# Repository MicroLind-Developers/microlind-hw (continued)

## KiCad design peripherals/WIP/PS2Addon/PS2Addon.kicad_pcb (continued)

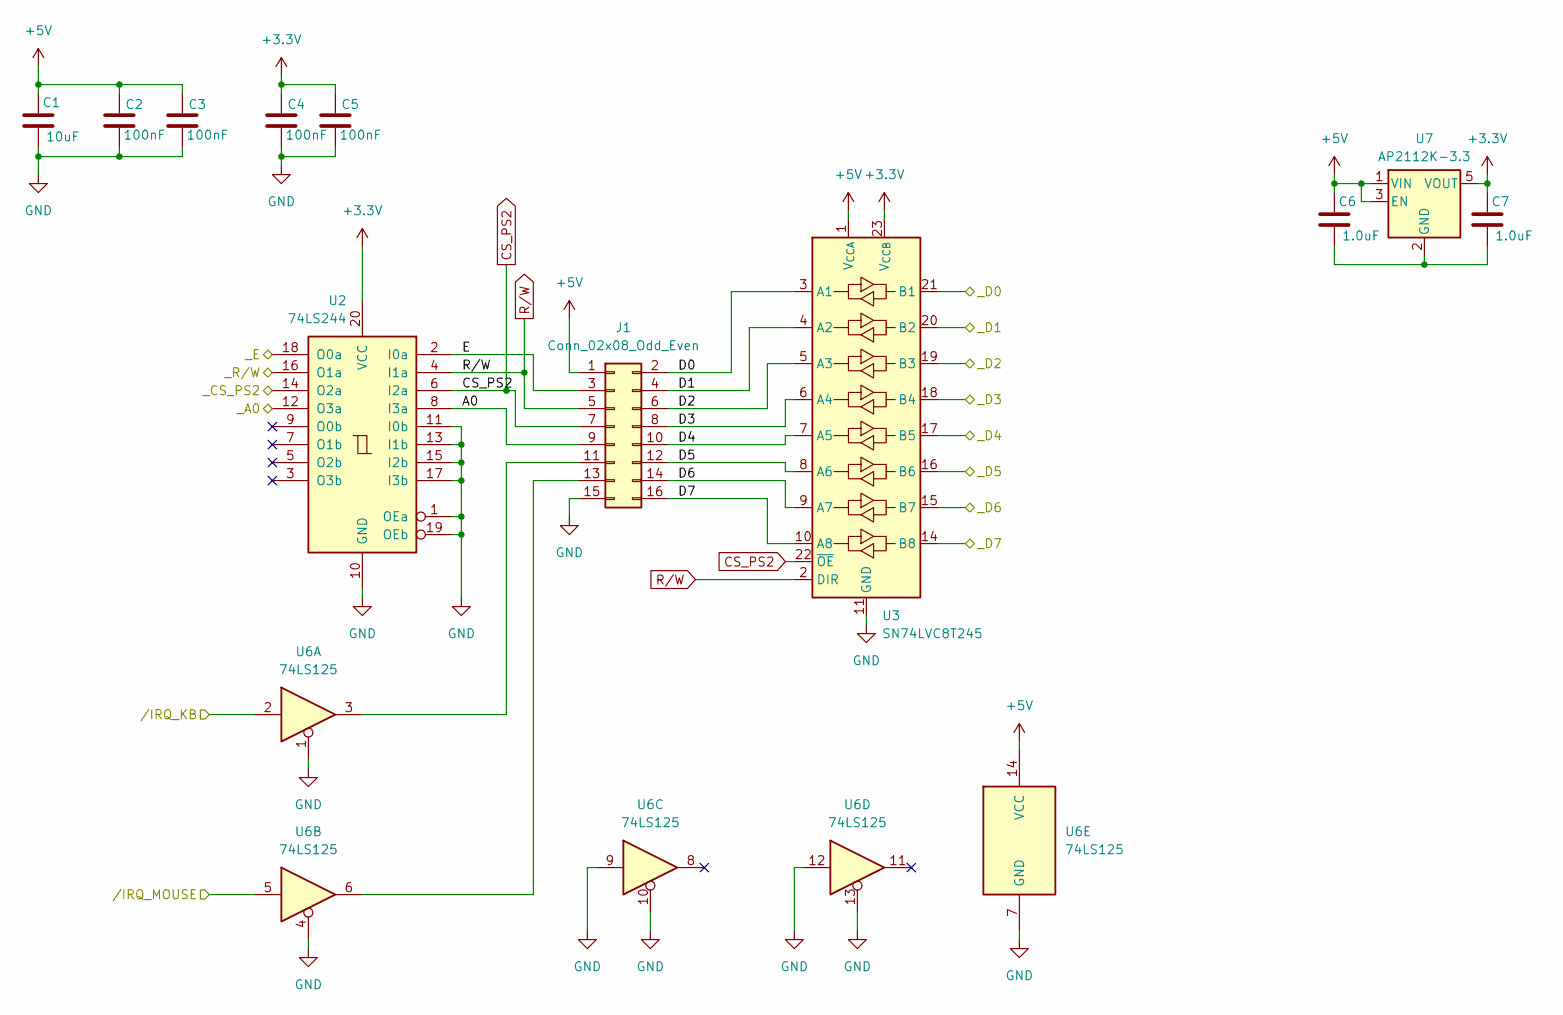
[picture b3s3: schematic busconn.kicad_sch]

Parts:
C1: 10uF; C_0402_1005Metric
C2, C3, C4, C5: 100nF; C_0402_1005Metric
C6, C7: 1.0uF; C_0402_1005Metric
J1: Conn_02x08_Odd_Even; PinHeader_2x08_P2.54mm_Vertical
U2: 74LS244; TSSOP-20_4.4x6.5mm_P0.65mm
U3: SN74LVC8T245; TSSOP-24_6.1x7.8mm_P0.65mm
U6: 74LS125; TSSOP-14_4.4x5mm_P0.65mm
U7: AP2112K-3.3; SOT-23-5

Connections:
+3.3V: C4.1, C5.1, C7.1, U2.20 (VCC), U3.23 (V_{CCB}), U3.24 (V_{CCB}), U7.5 (VOUT); also elsewhere on the board
+5V: C1.1, C2.1, C3.1, C6.1, J1.1, U3.1 (V_{CCA}), U6.14 (VCC), U7.1 (VIN), U7.3 (EN); also elsewhere on the board
/BusConnection/A0: J1.9, U2.8 (I3a)
/BusConnection/D0: J1.2, U3.3 (A1)
/BusConnection/D1: J1.4, U3.4 (A2)
/BusConnection/D2: J1.6, U3.5 (A3)
/BusConnection/D3: J1.8, U3.6 (A4)
/BusConnection/D4: J1.10, U3.7 (A5)
/BusConnection/D5: J1.12, U3.8 (A6)
/BusConnection/D6: J1.14, U3.9 (A7)
/BusConnection/D7: J1.16, U3.10 (A8)
/BusConnection/E: J1.3, U2.2 (I0a)
/BusConnection/_A0: U2.12 (O3a); also elsewhere on the board
/BusConnection/_CS_PS2: U2.14 (O2a); also elsewhere on the board
/BusConnection/_D0: U3.21 (B1); also elsewhere on the board
/BusConnection/_D1: U3.20 (B2); also elsewhere on the board
/BusConnection/_D2: U3.19 (B3); also elsewhere on the board
/BusConnection/_D3: U3.18 (B4); also elsewhere on the board
/BusConnection/_D4: U3.17 (B5); also elsewhere on the board
/BusConnection/_D5: U3.16 (B6); also elsewhere on the board
/BusConnection/_D6: U3.15 (B7); also elsewhere on the board
/BusConnection/_D7: U3.14 (B8); also elsewhere on the board
/BusConnection/_E: U2.18 (O0a); also elsewhere on the board
/BusConnection/_R/W: U2.16 (O1a); also elsewhere on the board
/BusConnection//IRQ_KB: U6.2; also elsewhere on the board
/BusConnection//IRQ_MOUSE: U6.5; also elsewhere on the board
CS_PS2: J1.7, U2.6 (I2a), U3.22 (~OE)
GND: C1.2, C2.2, C3.2, C4.2, C5.2, J1.15, U2.1 (OEa), U2.10 (GND), U2.11 (I0b), U2.13 (I1b), U2.15 (I2b), U2.17 (I3b), U2.19 (OEb), U3.11 (GND), U3.12 (GND), U3.13 (GND), U6.1, U6.4, U6.7 (GND), U6.9, U6.10, U6.12, U6.13; also elsewhere on the board
unnamed: J1.11, U6.3
unnamed: J1.13, U6.6
unnamed: C6.2, C7.2, U7.2 (GND)
R/W: J1.5, U2.4 (I1a), U3.2 (DIR)

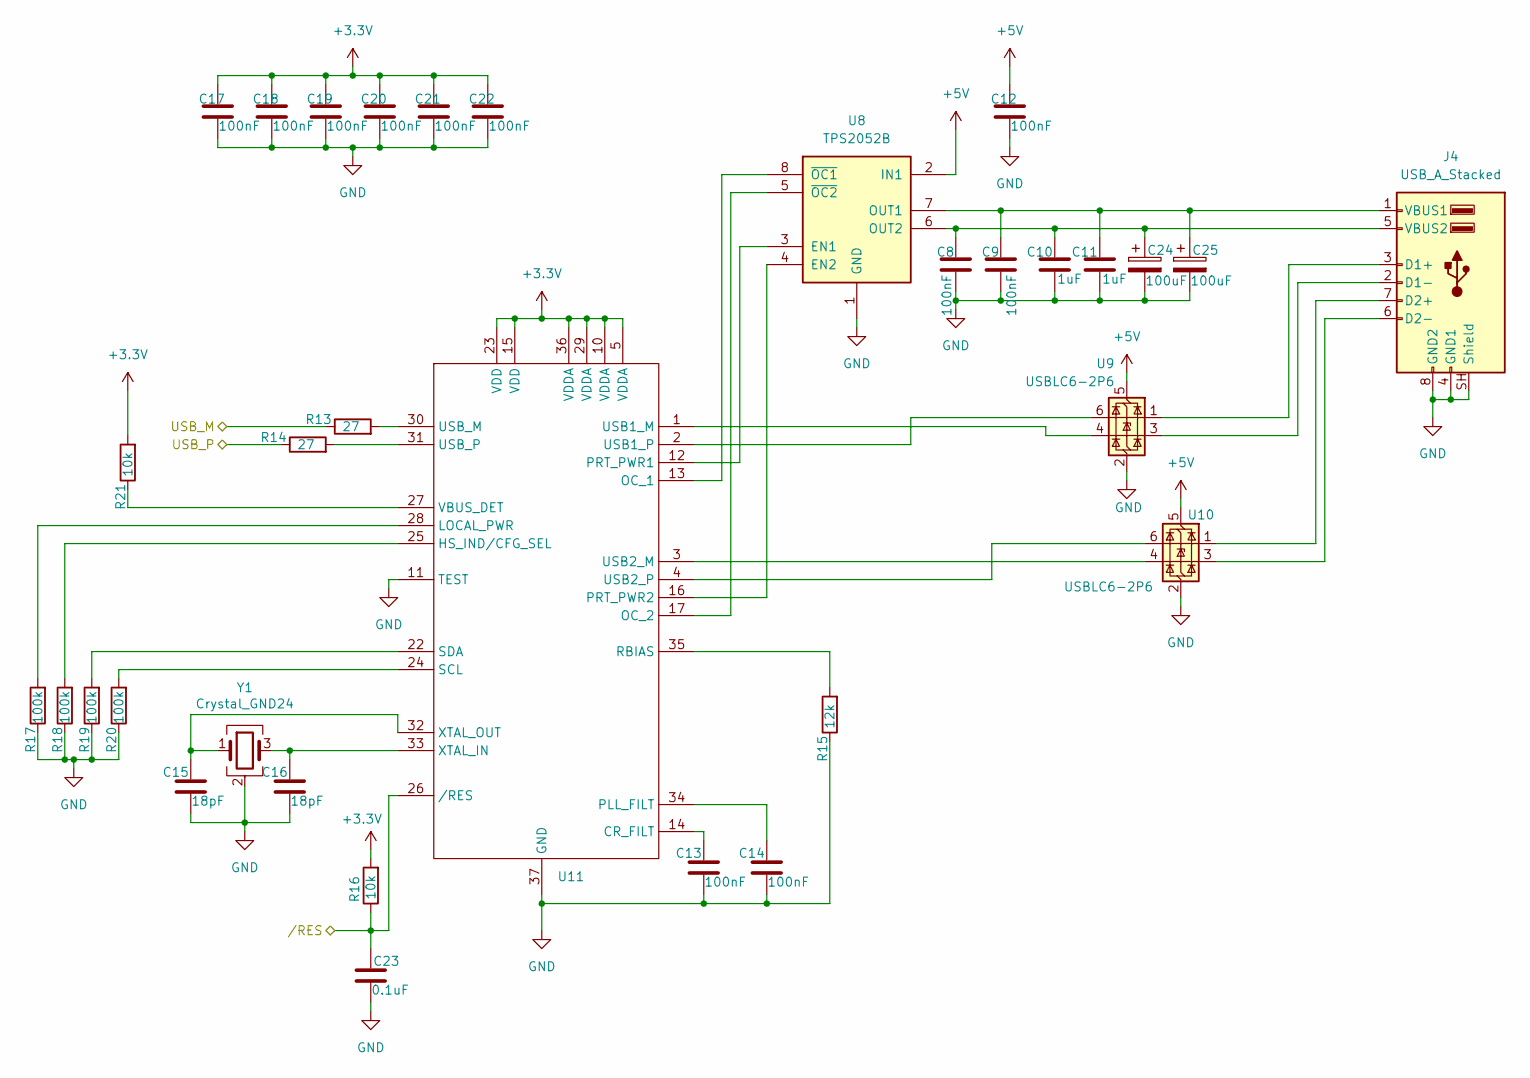
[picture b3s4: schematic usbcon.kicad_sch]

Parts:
C8, C9, C12, C13, C14, C17, C18, C19, C20, C21, C22: 100nF; C_0402_1005Metric
C10, C11: 1uF; C_0402_1005Metric
C15, C16: 18pF; C_0402_1005Metric
C23: 0.1uF; C_0402_1005Metric
C24, C25: 100uF; CP_EIA-1608-08_AVX-J
J4: USB_A_Stacked; USB_A_CUI_UJ2-ADH-TH_Horizontal_Stacked
R13, R14: 27; R_0402_1005Metric
R15: 12k; R_0402_1005Metric
R16, R21: 10k; R_0402_1005Metric
R17, R18, R19, R20: 100k; R_0402_1005Metric
U8: TPS2052B; SOIC-8_3.9x4.9mm_P1.27mm
U9, U10: USBLC6-2P6; SOT-666
U11: QFN-36-1EP_6x6mm_P0.5mm_EP4.1x4.1mm_ThermalVias
Y1: Crystal_GND24; Crystal_SMD_2520-4Pin_2.5x2.0mm

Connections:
+3.3V: C17.1, C18.1, C19.1, C20.1, C21.1, C22.1, R16.2, R21.2, U11.5 (VDDA), U11.10 (VDDA), U11.15 (VDD), U11.23 (VDD), U11.29 (VDDA), U11.36 (VDDA); also elsewhere on the board
+5V: C12.1, U8.2 (IN1), U9.5 (VBUS), U10.5 (VBUS); also elsewhere on the board
/USBConnector/USB_M: R13.1; also elsewhere on the board
/USBConnector/USB_P: R14.1; also elsewhere on the board
GND: C8.2, C9.2, C10.2, C11.2, C12.2, C13.2, C14.2, C15.2, C16.2, C17.2, C18.2, C19.2, C20.2, C21.2, C22.2, C23.2, C24.2, C25.2, J4.4 (GND1), J4.8 (GND2), J4.SH (Shield), R15.1, R17.1, R18.1, R19.1, R20.1, U8.1 (GND), U9.2 (GND), U10.2 (GND), U11.11 (TEST), U11.37 (GND), Y1.2 (G), Y1.4 (G); also elsewhere on the board
unnamed: J4.3 (D1+), U9.1 (I/O1)
unnamed: J4.2 (D1-), U9.3 (I/O2)
unnamed: J4.7 (D2+), U10.1 (I/O1)
unnamed: J4.6 (D2-), U10.3 (I/O2)
unnamed: C9.1, C11.1, C25.1, J4.1 (VBUS1), U8.7 (OUT1)
unnamed: C8.1, C10.1, C24.1, J4.5 (VBUS2), U8.6 (OUT2)
unnamed: C13.1, U11.14 (CR_FILT)
unnamed: R18.2, U11.25 (HS_IND/CFG_SEL)
unnamed: R17.2, U11.28 (LOCAL_PWR)
unnamed: U8.8 (~OC1), U11.13 (OC_1)
unnamed: U8.5 (~OC2), U11.17 (OC_2)
unnamed: C14.1, U11.34 (PLL_FILT)
unnamed: U8.3 (EN1), U11.12 (PRT_PWR1)
unnamed: U8.4 (EN2), U11.16 (PRT_PWR2)
unnamed: R15.2, U11.35 (RBIAS)
unnamed: R20.2, U11.24 (SCL)
unnamed: R19.2, U11.22 (SDA)
unnamed: U9.4 (I/O2), U11.1 (USB1_M)
unnamed: U9.6 (I/O1), U11.2 (USB1_P)
unnamed: U10.4 (I/O2), U11.3 (USB2_M)
unnamed: U10.6 (I/O1), U11.4 (USB2_P)
unnamed: R13.2, U11.30 (USB_M)
unnamed: R14.2, U11.31 (USB_P)
unnamed: R21.1, U11.27 (VBUS_DET)
unnamed: C16.1, U11.33 (XTAL_IN), Y1.3
unnamed: C15.1, U11.32 (XTAL_OUT), Y1.1
/USB_RES: C23.1, R16.1, U11.26 (/RES); also elsewhere on the board

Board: 2 copper layers, 82 parts (0 on the bottom side), 80 nets, no tracks yet.

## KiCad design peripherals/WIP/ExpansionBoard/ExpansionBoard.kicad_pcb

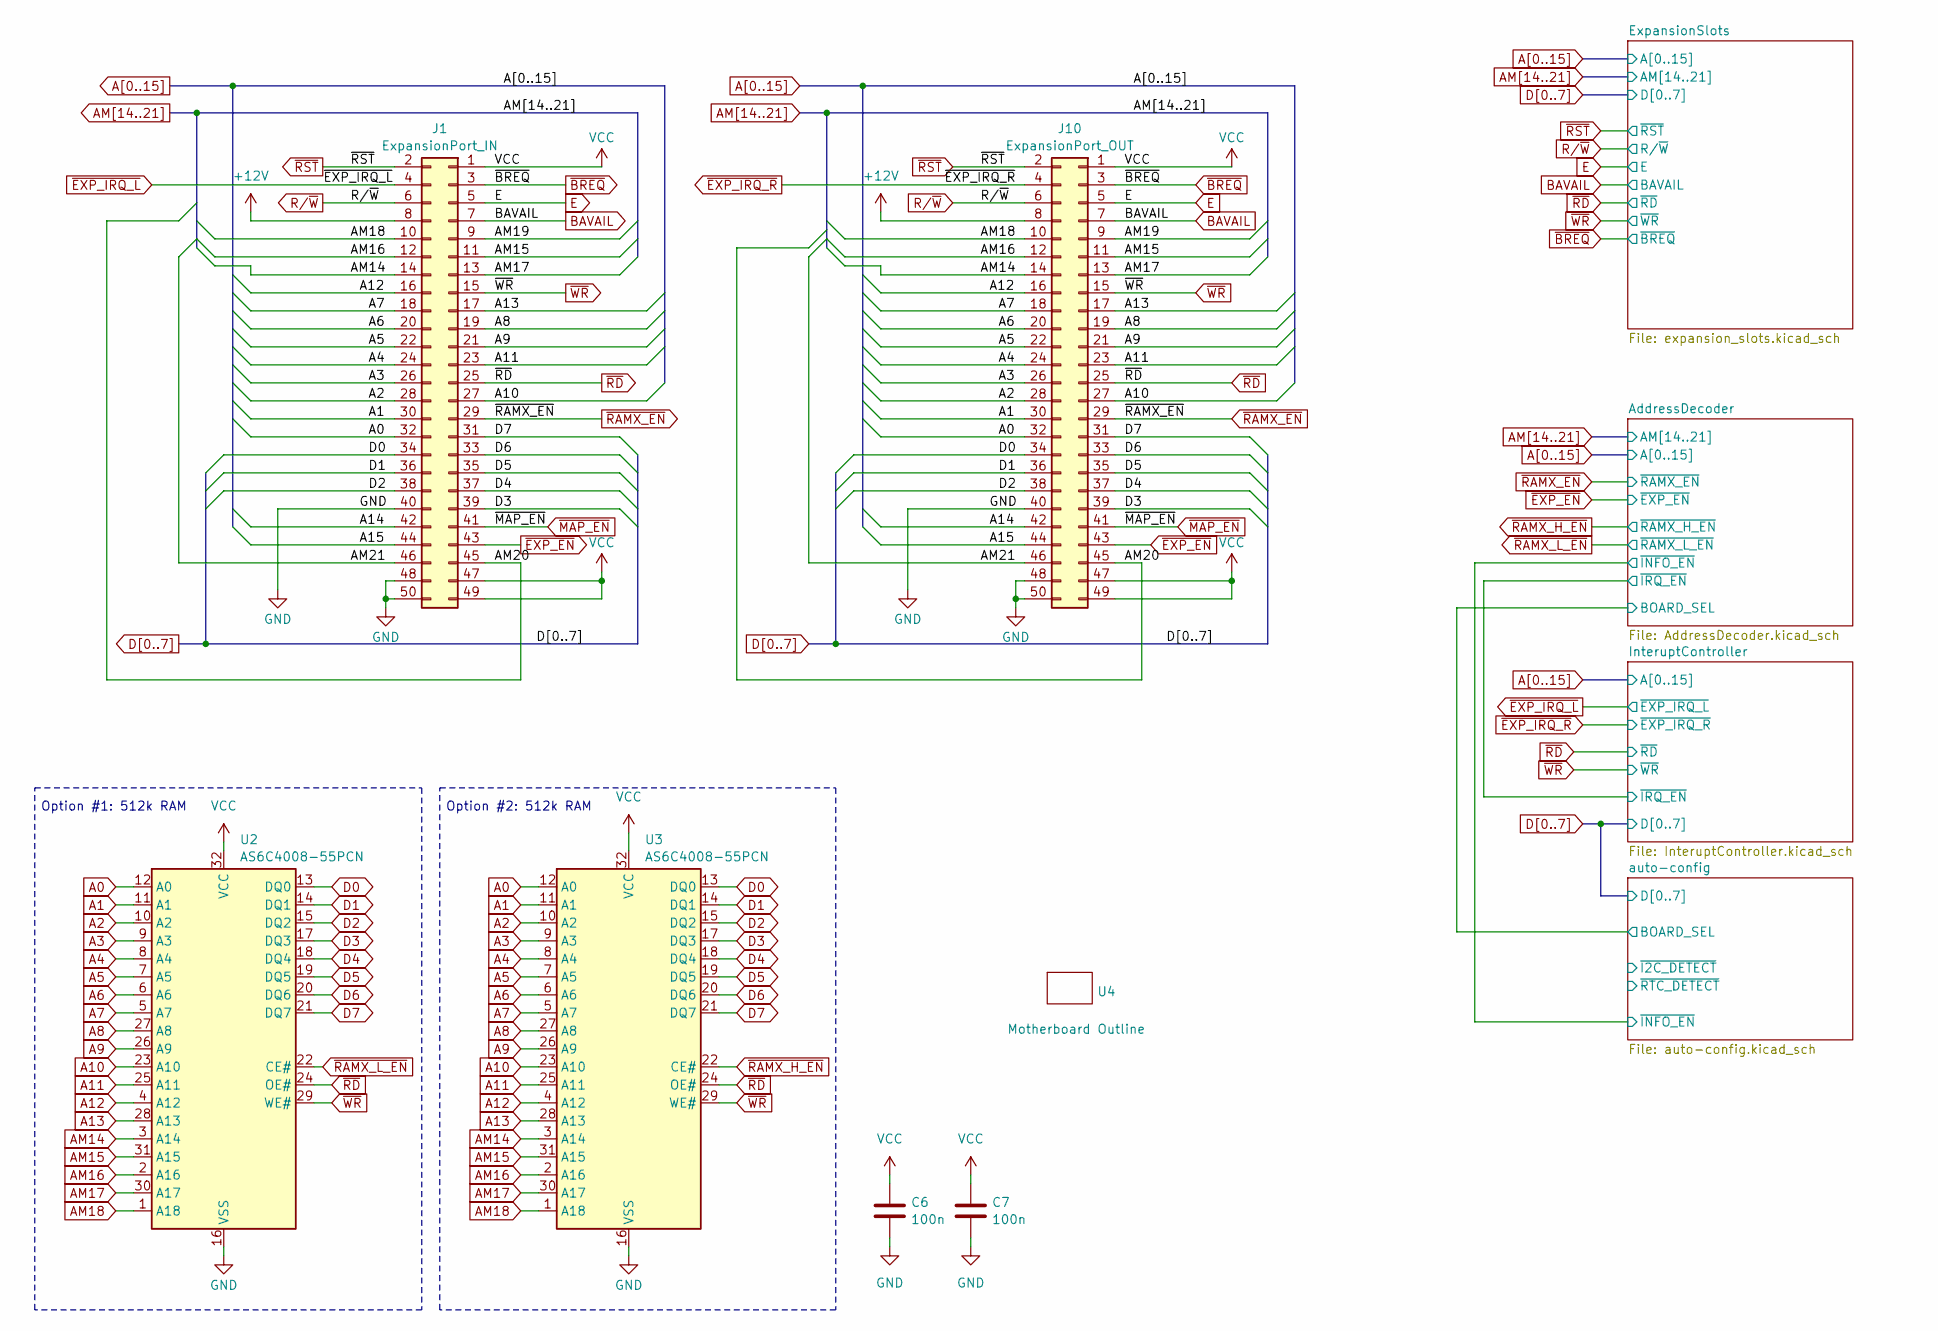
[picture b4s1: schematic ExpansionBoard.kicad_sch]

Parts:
C6, C7: 100n; C_Disc_D3.0mm_W1.6mm_P2.50mm
J1: ExpansionPort_IN; PinSocket_2x25_P2.54mm_Vertical
J10: ExpansionPort_OUT; PinSocket_2x25_P2.54mm_Vertical
U2, U3: AS6C4008-55PCN; DIP-32_W15.24mm_Socket
U4: Motherboard Outline; mITX

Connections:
+12V: J1.8, J10.8; also elsewhere on the board
A0: J1.32, J10.32, U2.12 (A0), U3.12 (A0); also elsewhere on the board
A1: J1.30, J10.30, U2.11 (A1), U3.11 (A1); also elsewhere on the board
A2: J1.28, J10.28, U2.10 (A2), U3.10 (A2); also elsewhere on the board
A3: J1.26, J10.26, U2.9 (A3), U3.9 (A3); also elsewhere on the board
A4: J1.24, J10.24, U2.8 (A4), U3.8 (A4); also elsewhere on the board
A5: J1.22, J10.22, U2.7 (A5), U3.7 (A5); also elsewhere on the board
A6: J1.20, J10.20, U2.6 (A6), U3.6 (A6); also elsewhere on the board
A7: J1.18, J10.18, U2.5 (A7), U3.5 (A7); also elsewhere on the board
A8: J1.19, J10.19, U2.27 (A8), U3.27 (A8); also elsewhere on the board
A9: J1.21, J10.21, U2.26 (A9), U3.26 (A9); also elsewhere on the board
A10: J1.27, J10.27, U2.23 (A10), U3.23 (A10); also elsewhere on the board
A11: J1.23, J10.23, U2.25 (A11), U3.25 (A11); also elsewhere on the board
A12: J1.16, J10.16, U2.4 (A12), U3.4 (A12); also elsewhere on the board
A13: J1.17, J10.17, U2.28 (A13), U3.28 (A13); also elsewhere on the board
A14: J1.42, J10.42; also elsewhere on the board
A15: J1.44, J10.44; also elsewhere on the board
AM14: J1.14, J10.14, U2.3 (A14), U3.3 (A14); also elsewhere on the board
AM15: J1.11, J10.11, U2.31 (A15), U3.31 (A15); also elsewhere on the board
AM16: J1.12, J10.12, U2.2 (A16), U3.2 (A16); also elsewhere on the board
AM17: J1.13, J10.13, U2.30 (A17), U3.30 (A17); also elsewhere on the board
AM18: J1.10, J10.10, U2.1 (A18), U3.1 (A18); also elsewhere on the board
AM19: J1.9, J10.9; also elsewhere on the board
AM20: J1.45, J10.45; also elsewhere on the board
AM21: J1.46, J10.46; also elsewhere on the board
BAVAIL: J1.7, J10.7; also elsewhere on the board
D0: J1.34, J10.34, U2.13 (DQ0), U3.13 (DQ0); also elsewhere on the board
D1: J1.36, J10.36, U2.14 (DQ1), U3.14 (DQ1); also elsewhere on the board
D2: J1.38, J10.38, U2.15 (DQ2), U3.15 (DQ2); also elsewhere on the board
D3: J1.39, J10.39, U2.17 (DQ3), U3.17 (DQ3); also elsewhere on the board
D4: J1.37, J10.37, U2.18 (DQ4), U3.18 (DQ4); also elsewhere on the board
D5: J1.35, J10.35, U2.19 (DQ5), U3.19 (DQ5); also elsewhere on the board
D6: J1.33, J10.33, U2.20 (DQ6), U3.20 (DQ6); also elsewhere on the board
D7: J1.31, J10.31, U2.21 (DQ7), U3.21 (DQ7); also elsewhere on the board
E: J1.5, J10.5; also elsewhere on the board
GND: C6.2, C7.2, J1.40, J1.48, J1.50, J10.40, J10.48, J10.50, U2.16 (VSS), U3.16 (VSS); also elsewhere on the board
R/~W: J1.6, J10.6; also elsewhere on the board
VCC: C6.1, C7.1, J1.1, J1.47, J1.49, J10.1, J10.47, J10.49, U2.32 (VCC), U3.32 (VCC); also elsewhere on the board
~BREQ: J1.3, J10.3; also elsewhere on the board
~EXP_EN: J1.43, J10.43; also elsewhere on the board
~EXP_IRQ_L: J1.4; also elsewhere on the board
~EXP_IRQ_R: J10.4; also elsewhere on the board
~MAP_EN: J1.41, J10.41; also elsewhere on the board
~RAMX_EN: J1.29, J10.29; also elsewhere on the board
~RAMX_H_EN: U3.22 (CE#); also elsewhere on the board
~RAMX_L_EN: U2.22 (CE#); also elsewhere on the board
~RD: J1.25, J10.25, U2.24 (OE#), U3.24 (OE#); also elsewhere on the board
~RST: J1.2, J10.2; also elsewhere on the board
~WR: J1.15, J10.15, U2.29 (WE#), U3.29 (WE#); also elsewhere on the board

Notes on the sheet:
Option #1: 512k RAM
Option #2: 512k RAM

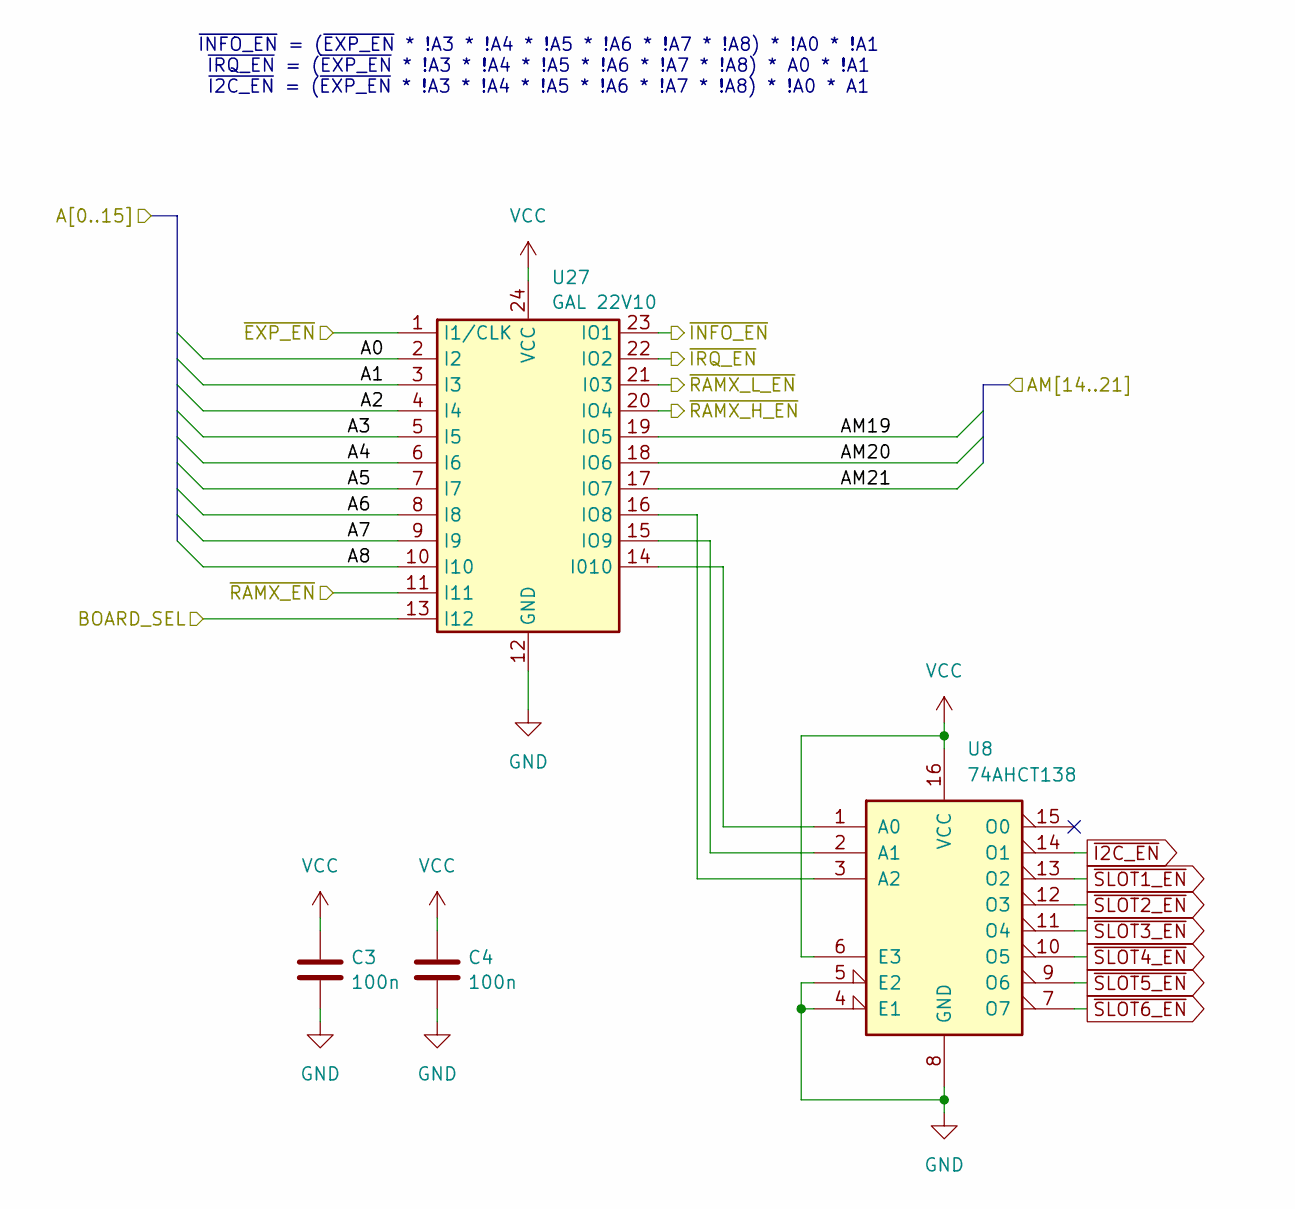
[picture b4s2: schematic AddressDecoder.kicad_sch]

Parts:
C3, C4: 100n; C_Disc_D3.0mm_W1.6mm_P2.50mm
U8: 74AHCT138; DIP-16_W7.62mm_Socket
U27: GAL 22V10; DIP-24_W7.62mm_Socket

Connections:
/AddressDecoder/~INFO_EN: U27.23 (IO1); also elsewhere on the board
/AddressDecoder/~IRQ_EN: U27.22 (IO2); also elsewhere on the board
/auto-config/BOARD_ADDRESS_SELECT: U27.13 (I12); also elsewhere on the board
A0: U27.2 (I2); also elsewhere on the board
A1: U27.3 (I3); also elsewhere on the board
A2: U27.4 (I4); also elsewhere on the board
A3: U27.5 (I5); also elsewhere on the board
A4: U27.6 (I6); also elsewhere on the board
A5: U27.7 (I7); also elsewhere on the board
A6: U27.8 (I8); also elsewhere on the board
A7: U27.9 (I9); also elsewhere on the board
A8: U27.10 (I10); also elsewhere on the board
AM19: U27.19 (IO5); also elsewhere on the board
AM20: U27.18 (IO6); also elsewhere on the board
AM21: U27.17 (IO7); also elsewhere on the board
GND: C3.2, C4.2, U8.4 (E1), U8.5 (E2), U8.8 (GND), U27.12 (GND); also elsewhere on the board
unnamed: U8.1 (A0), U27.14 (I010)
unnamed: U8.3 (A2), U27.16 (IO8)
unnamed: U8.2 (A1), U27.15 (IO9)
VCC: C3.1, C4.1, U8.6 (E3), U8.16 (VCC), U27.24 (VCC); also elsewhere on the board
~EXP_EN: U27.1 (I1/CLK); also elsewhere on the board
~I2C_EN: U8.14 (O1); also elsewhere on the board
~RAMX_EN: U27.11 (I11); also elsewhere on the board
~RAMX_H_EN: U27.20 (IO4); also elsewhere on the board
~RAMX_L_EN: U27.21 (I03); also elsewhere on the board
~SLOT1_EN: U8.13 (O2)
~SLOT2_EN: U8.12 (O3)
~SLOT3_EN: U8.11 (O4)
~SLOT4_EN: U8.10 (O5)
~SLOT5_EN: U8.9 (O6)
~SLOT6_EN: U8.7 (O7)

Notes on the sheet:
~{INFO_EN} = (~{EXP_EN} * !A3 * !A4 * !A5 * !A6 * !A7 * !A8) * !A0 * !A1 ~{IRQ_EN} = (~{EXP_EN} * !A3 * !A4 * !A5 * !A6 * !A7 * !A8) * A0 * !A1 ~{I2C_EN} = (~{EXP_EN} * !A3 * !A4 * !A5 * !A6 * !A7 * !A8) * !A0 * A1

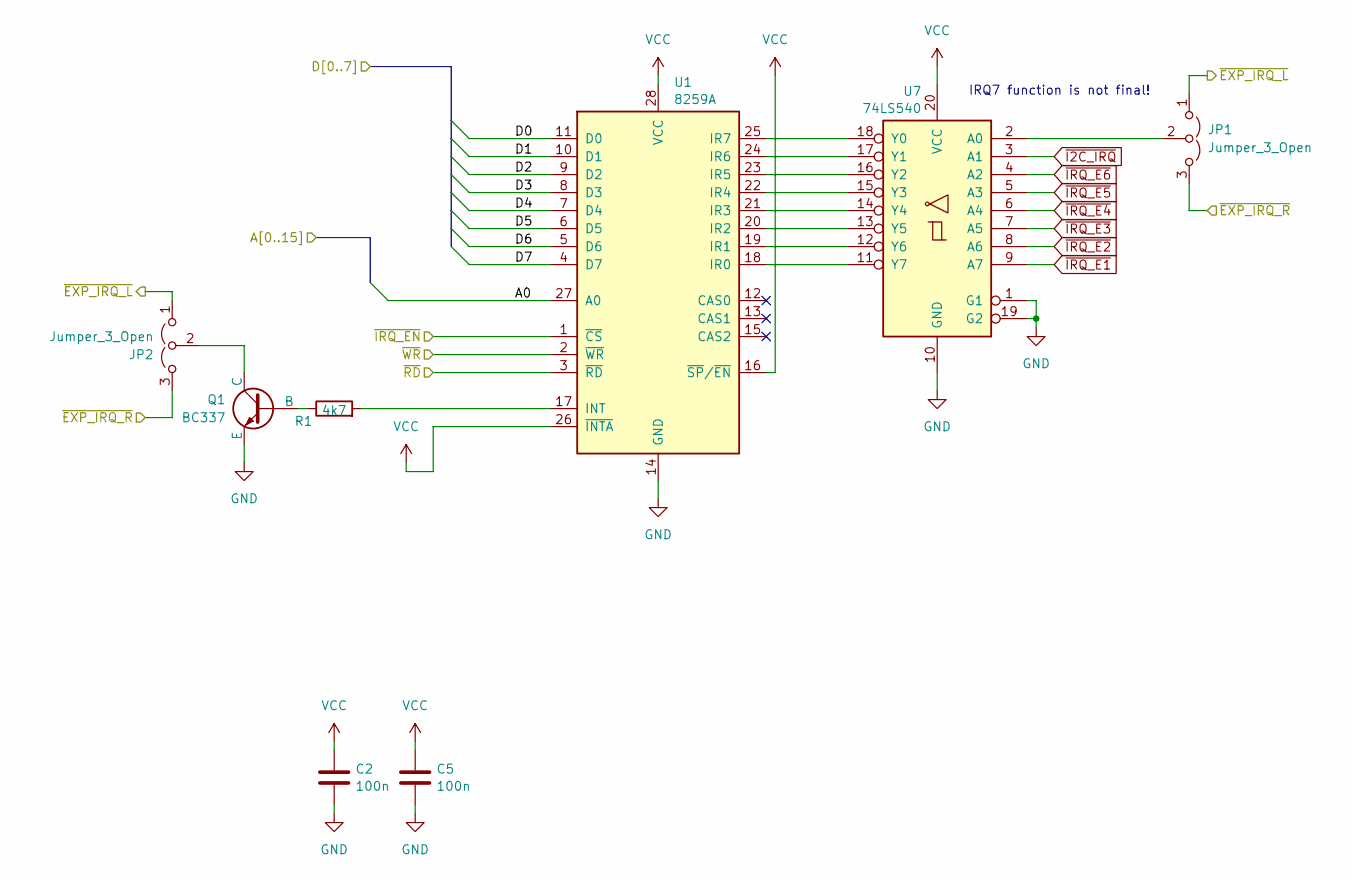
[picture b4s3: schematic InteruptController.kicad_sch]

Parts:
C2, C5: 100n; C_Disc_D3.0mm_W1.6mm_P2.50mm
JP1, JP2: Jumper_3_Open; PinHeader_1x03_P2.54mm_Vertical
Q1: BC337; TO-92
R1: 4k7; R_Axial_DIN0207_L6.3mm_D2.5mm_P7.62mm_Horizontal
U1: 8259A; DIP-28_W15.24mm_Socket
U7: 74LS540; DIP-20_W7.62mm_Socket

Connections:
/AddressDecoder/~IRQ_EN: U1.1 (~CS); also elsewhere on the board
A0: U1.27 (A0); also elsewhere on the board
D0: U1.11 (D0); also elsewhere on the board
D1: U1.10 (D1); also elsewhere on the board
D2: U1.9 (D2); also elsewhere on the board
D3: U1.8 (D3); also elsewhere on the board
D4: U1.7 (D4); also elsewhere on the board
D5: U1.6 (D5); also elsewhere on the board
D6: U1.5 (D6); also elsewhere on the board
D7: U1.4 (D7); also elsewhere on the board
GND: C2.2, C5.2, Q1.3 (E), U1.14 (GND), U7.1 (G1), U7.10 (GND), U7.19 (G2); also elsewhere on the board
unnamed: JP1.2 (C), U7.2 (A0)
unnamed: JP2.2 (C), Q1.1 (C)
unnamed: Q1.2 (B), R1.1
unnamed: R1.2, U1.17 (INT)
unnamed: U1.18 (IR0), U7.11 (Y7)
unnamed: U1.19 (IR1), U7.12 (Y6)
unnamed: U1.20 (IR2), U7.13 (Y5)
unnamed: U1.21 (IR3), U7.14 (Y4)
unnamed: U1.22 (IR4), U7.15 (Y3)
unnamed: U1.23 (IR5), U7.16 (Y2)
unnamed: U1.24 (IR6), U7.17 (Y1)
unnamed: U1.25 (IR7), U7.18 (Y0)
VCC: C2.1, C5.1, U1.16 (~SP/~EN), U1.26 (~INTA), U1.28 (VCC), U7.20 (VCC); also elsewhere on the board
~EXP_IRQ_L: JP1.1 (A), JP2.1 (A); also elsewhere on the board
~EXP_IRQ_R: JP1.3 (B), JP2.3 (B); also elsewhere on the board
~I2C_IRQ: U7.3 (A1); also elsewhere on the board
~IRQ_E1: U7.9 (A7); also elsewhere on the board
~IRQ_E2: U7.8 (A6); also elsewhere on the board
~IRQ_E3: U7.7 (A5); also elsewhere on the board
~IRQ_E4: U7.6 (A4); also elsewhere on the board
~IRQ_E5: U7.5 (A3); also elsewhere on the board
~IRQ_E6: U7.4 (A2); also elsewhere on the board
~RD: U1.3 (~RD); also elsewhere on the board
~WR: U1.2 (~WR); also elsewhere on the board

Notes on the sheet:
IRQ7 function is not final!

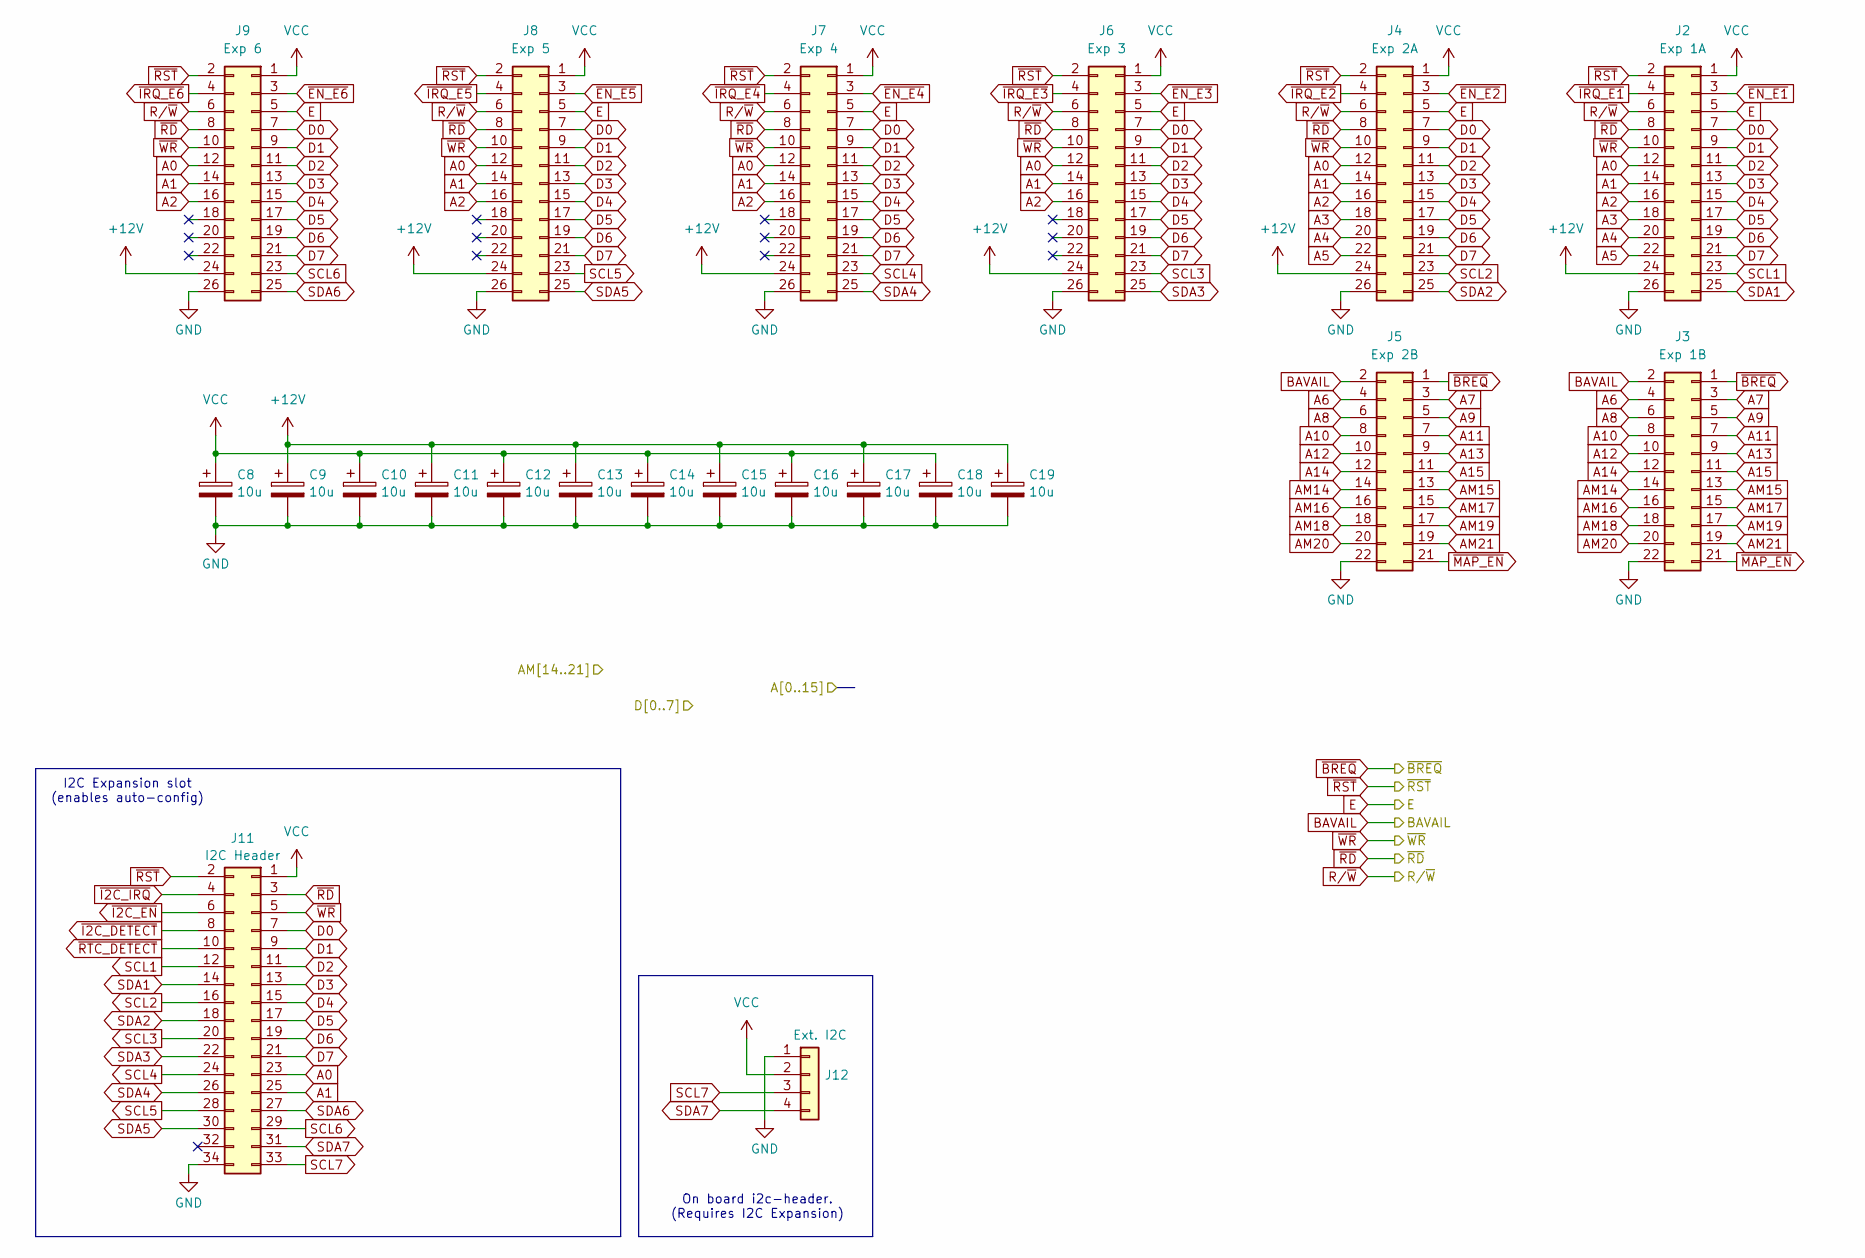
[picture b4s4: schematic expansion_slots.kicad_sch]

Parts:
C8, C9, C10, C11, C12, C13, C14, C15, C16, C17, C18, C19: 10u; CP_Radial_D5.0mm_P2.00mm
J2: Exp 1A; PinSocket_2x13_P2.54mm_Vertical
J3: Exp 1B; PinSocket_2x11_P2.54mm_Vertical
J4: Exp 2A; PinSocket_2x13_P2.54mm_Vertical
J5: Exp 2B; PinSocket_2x11_P2.54mm_Vertical
J6: Exp 3; PinSocket_2x13_P2.54mm_Vertical
J7: Exp 4; PinSocket_2x13_P2.54mm_Vertical
J8: Exp 5; PinSocket_2x13_P2.54mm_Vertical
J9: Exp 6; PinSocket_2x13_P2.54mm_Vertical
J11: I2C Header; PinSocket_2x17_P2.54mm_Vertical
J12: Ext. I2C; PinSocket_1x04_P2.54mm_Vertical

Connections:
+12V: C9.1, C11.1, C13.1, C15.1, C17.1, C19.1, J2.24, J4.24, J6.24, J7.24, J8.24, J9.24; also elsewhere on the board
A0: J2.12, J4.12, J6.12, J7.12, J8.12, J9.12, J11.23; also elsewhere on the board
A1: J2.14, J4.14, J6.14, J7.14, J8.14, J9.14, J11.25; also elsewhere on the board
A2: J2.16, J4.16, J6.16, J7.16, J8.16, J9.16; also elsewhere on the board
A3: J2.18, J4.18; also elsewhere on the board
A4: J2.20, J4.20; also elsewhere on the board
A5: J2.22, J4.22; also elsewhere on the board
A6: J3.4, J5.4; also elsewhere on the board
A7: J3.3, J5.3; also elsewhere on the board
A8: J3.6, J5.6; also elsewhere on the board
A9: J3.5, J5.5; also elsewhere on the board
A10: J3.8, J5.8; also elsewhere on the board
A11: J3.7, J5.7; also elsewhere on the board
A12: J3.10, J5.10; also elsewhere on the board
A13: J3.9, J5.9; also elsewhere on the board
A14: J3.12, J5.12; also elsewhere on the board
A15: J3.11, J5.11; also elsewhere on the board
AM14: J3.14, J5.14; also elsewhere on the board
AM15: J3.13, J5.13; also elsewhere on the board
AM16: J3.16, J5.16; also elsewhere on the board
AM17: J3.15, J5.15; also elsewhere on the board
AM18: J3.18, J5.18; also elsewhere on the board
AM19: J3.17, J5.17; also elsewhere on the board
AM20: J3.20, J5.20; also elsewhere on the board
AM21: J3.19, J5.19; also elsewhere on the board
BAVAIL: J3.2, J5.2; also elsewhere on the board
D0: J2.7, J4.7, J6.7, J7.7, J8.7, J9.7, J11.7; also elsewhere on the board
D1: J2.9, J4.9, J6.9, J7.9, J8.9, J9.9, J11.9; also elsewhere on the board
D2: J2.11, J4.11, J6.11, J7.11, J8.11, J9.11, J11.11; also elsewhere on the board
D3: J2.13, J4.13, J6.13, J7.13, J8.13, J9.13, J11.13; also elsewhere on the board
D4: J2.15, J4.15, J6.15, J7.15, J8.15, J9.15, J11.15; also elsewhere on the board
D5: J2.17, J4.17, J6.17, J7.17, J8.17, J9.17, J11.17; also elsewhere on the board
D6: J2.19, J4.19, J6.19, J7.19, J8.19, J9.19, J11.19; also elsewhere on the board
D7: J2.21, J4.21, J6.21, J7.21, J8.21, J9.21, J11.21; also elsewhere on the board
E: J2.5, J4.5, J6.5, J7.5, J8.5, J9.5; also elsewhere on the board
GND: C8.2, C9.2, C10.2, C11.2, C12.2, C13.2, C14.2, C15.2, C16.2, C17.2, C18.2, C19.2, J2.26, J3.22, J4.26, J5.22, J6.26, J7.26, J8.26, J9.26, J11.34, J12.1; also elsewhere on the board
R/~W: J2.6, J4.6, J6.6, J7.6, J8.6, J9.6; also elsewhere on the board
SCL1: J2.23, J11.12
SCL2: J4.23, J11.16
SCL3: J6.23, J11.20
SCL4: J7.23, J11.24
SCL5: J8.23, J11.28
SCL6: J9.23, J11.29
SCL7: J11.33, J12.3
SDA1: J2.25, J11.14
SDA2: J4.25, J11.18
SDA3: J6.25, J11.22
SDA4: J7.25, J11.26
SDA5: J8.25, J11.30
SDA6: J9.25, J11.27
SDA7: J11.31, J12.4
VCC: C8.1, C10.1, C12.1, C14.1, C16.1, C18.1, J2.1, J4.1, J6.1, J7.1, J8.1, J9.1, J11.1, J12.2; also elsewhere on the board
~BREQ: J3.1, J5.1; also elsewhere on the board
~EN_E1: J2.3
~EN_E2: J4.3
~EN_E3: J6.3
~EN_E4: J7.3
~EN_E5: J8.3
~EN_E6: J9.3
~I2C_DETECT: J11.8
~I2C_EN: J11.6; also elsewhere on the board
~I2C_IRQ: J11.4; also elsewhere on the board
~IRQ_E1: J2.4; also elsewhere on the board
~IRQ_E2: J4.4; also elsewhere on the board
~IRQ_E3: J6.4; also elsewhere on the board
~IRQ_E4: J7.4; also elsewhere on the board
~IRQ_E5: J8.4; also elsewhere on the board
~IRQ_E6: J9.4; also elsewhere on the board
~MAP_EN: J3.21, J5.21; also elsewhere on the board
~RD: J2.8, J4.8, J6.8, J7.8, J8.8, J9.8, J11.3; also elsewhere on the board
~RST: J2.2, J4.2, J6.2, J7.2, J8.2, J9.2, J11.2; also elsewhere on the board
~RTC_DETECT: J11.10
~WR: J2.10, J4.10, J6.10, J7.10, J8.10, J9.10, J11.5; also elsewhere on the board

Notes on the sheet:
On board i2c-header. (Requires I2C Expansion)
I2C Expansion slot (enables auto-config)

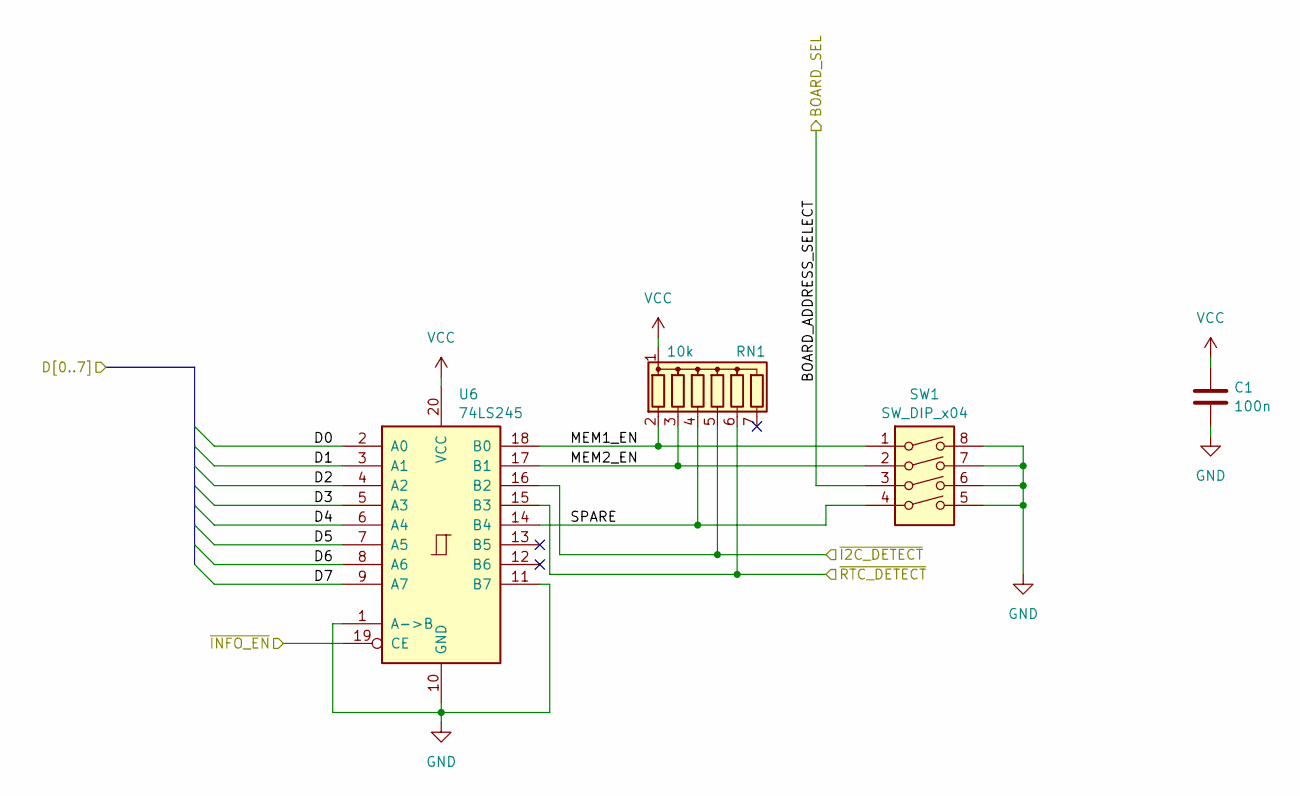
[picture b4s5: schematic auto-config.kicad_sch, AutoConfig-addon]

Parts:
C1: 100n; C_Disc_D3.0mm_W1.6mm_P2.50mm
RN1: 10k; R_Array_SIP7
SW1: SW_DIP_x04; PinHeader_2x04_P2.54mm_Vertical
U6: 74LS245; DIP-20_W7.62mm_Socket

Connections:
/AddressDecoder/~INFO_EN: U6.19 (CE); also elsewhere on the board
/auto-config/BOARD_ADDRESS_SELECT: SW1.3; also elsewhere on the board
/auto-config/MEM1_EN: RN1.2 (R1), SW1.1, U6.18 (B0)
/auto-config/MEM2_EN: RN1.3 (R2), SW1.2, U6.17 (B1)
/auto-config/SPARE: RN1.4 (R3), SW1.4, U6.14 (B4)
/auto-config/~I2C_DETECT: RN1.5 (R4), U6.16 (B2)
/auto-config/~RTC_DETECT: RN1.6 (R5), U6.15 (B3)
D0: U6.2 (A0); also elsewhere on the board
D1: U6.3 (A1); also elsewhere on the board
D2: U6.4 (A2); also elsewhere on the board
D3: U6.5 (A3); also elsewhere on the board
D4: U6.6 (A4); also elsewhere on the board
D5: U6.7 (A5); also elsewhere on the board
D6: U6.8 (A6); also elsewhere on the board
D7: U6.9 (A7); also elsewhere on the board
GND: C1.2, SW1.5, SW1.6, SW1.7, SW1.8, U6.1 (A->B), U6.10 (GND), U6.11 (B7); also elsewhere on the board
VCC: C1.1, RN1.1 (common), U6.20 (VCC); also elsewhere on the board
